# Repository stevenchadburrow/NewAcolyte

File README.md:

# NewAcolyte

This is the New Acolyte microcomputer.  

It runs a W65C02 microprocessor at 6.29 MHz, and has 64 KB of RAM and 32 KB of ROM available.  It can output 16-colors at a 256x240 resolution, or 4-colors at 512x240 resolution.  It supports PS/2 Keyboard and Mouse, Genesis Gamepad, square wave audio output, and SD Card through SPI adapter.  This New Acolyte uses the Xilinx XC9572XL CLPD, programmed using Xilinx ISE and 'xc3sprog'.  

Currently it's software includes the Scratchpad, Monitor, BASIC, and games including Tetra, Intruders, Missile, Galian, and Knave.

(Bodge wire connects V-SYNC to /NMI. Additional pull-up resistors on JOY-UP, JOY-DOWN, JOY-BUTTON1, and JOY-BUTTON2. Additional pull-down resistor on ROM-BANK.)

<br>
<br>
<br>
<br>
<br>

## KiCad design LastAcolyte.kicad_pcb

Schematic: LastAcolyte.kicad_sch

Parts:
C1: C_Polarized_US; CP_Elec_6.3x5.4
C2, C16: C-Polarized-US; CP_Elec_4x5.4
C3, C4, C5, C6, C7, C8, C9, C10, C11, C12, C13, C14, C17, C18: C; C_1206_3216Metric_Pad1.33x1.80mm_HandSolder
C15: C_Polarized_US; CP_Elec_4x5.4
D1: LED; LED_1206_3216Metric_Pad1.42x1.75mm_HandSolder
J1: USB_B; DualPowerSupply
J2: Mini-DIN-6; PS2_Din6
J3: AudioJack3; Jack_3.5mm_CUI_custom_SJ-3524-SMT_Horizontal
J4: DB15_Female_HighDensity; DSUB-15-HD_Female_Horizontal_P2.29x2.54mm_VGA
J5: Conn-01x06; SDcardPinSocket-Plus
J6, J7: Conn_02x10_Odd_Even; PinHeader_2x10_P2.54mm_Horizontal
J8: DB9_Male; DSUB-9-custom_Male_Horizontal_P2.77x2.84mm_EdgePinOffset7.7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
J9: Conn_02x05_Odd_Even; PinHeader_2x05_P2.54mm_Vertical
JP2: SolderJumper_2_Open; SolderJumper_Testing-2_P1.3mm_Open_Pad1.0x1.5mm
R1, R4, R5, R6, R7, R9, R10, R11, R12, R13, R14, R15, R16, R17, R18, R19, R20, R21, R22, R23, R24, R25, R26, R27: R_US; R_1206_3216Metric_Pad1.30x1.75mm_HandSolder
R2, R3, R8: R-US; R_1206_3216Metric_Pad1.30x1.75mm_HandSolder
SW1: SW_SPDT; SPDT-100SP1T2B4M6QE
SW2: SW_Push; SW_Tactile_SPST_Angled_PTS645Vx83-2LFS
TP1, TP2, TP3, TP4: TestPoint; ScrewHole-4-40
U1: W65C02SxPL; PLCC-44_THT-Socket
U2: IS62C1024AL-35; SSOP-32_11.305x20.495mm_P1.27mm
U3: SST39SF010-55; PLCC-32_THT-Socket
U4: LD1117S33; SOT-223-3_TabPin2
U5: XC9572XLVQ44; TQFP-44_10x10mm_P0.8mm
U6: 74HCT574; SOIC-20W_7.5x12.8mm_P1.27mm
U7: W65C22SxPL; PLCC-44_THT-Socket
U8: MCP130-xxxxSN; SOIC-8_3.9x4.9mm_P1.27mm
X1: CXO_DIP8; Oscillator_DIP-8-custom

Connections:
+3.3V: C10.1, C11.1, C12.1, C15.1, J9.4, R1.2, R9.1, R10.1, R11.1, R12.1, U4.2 (VO), U5.15 (VCC), U5.26 (VCCIO), U5.35 (VCC)
+5V: C1.1, C3.1, C4.1, C5.1, C6.1, C7.1, C8.1, C9.1, C13.1, C14.1, C17.1, C18.1, J2.4, J5.2, J6.1, J6.19, J7.2, J7.19, J8.5, JP2.2 (B), R4.1, R5.1, R6.1, R7.2, R18.1, R19.2, R20.2, R22.2, R23.1, R24.1, R25.2, R26.2, R27.2, SW1.2 (B), U1.9 (VDD), U1.37 (VDD), U2.1 (A18), U2.30 (A17), U2.32 (VCC), U3.31 (PGM), U3.32 (VCC), U4.3 (VI), U6.20 (VCC), U7.21 (VDD), U7.26 (CS1), U8.2 (VDD), X1.8 (Vcc)
/A0: U1.10 (A0), U2.12 (A0), U3.12 (A0), U6.12 (Q7), U7.42 (RS0)
/A1: U1.11 (A1), U2.11 (A1), U3.11 (A1), U6.13 (Q6), U7.41 (RS1)
/A2: U1.13 (A2), U2.10 (A2), U3.10 (A2), U6.14 (Q5), U7.40 (RS2)
/A3: U1.14 (A3), U2.9 (A3), U3.9 (A3), U6.15 (Q4), U7.39 (RS3)
/A4: U1.15 (A4), U2.8 (A4), U3.8 (A4), U6.16 (Q3)
/A5: U1.16 (A5), U2.7 (A5), U3.7 (A5), U6.17 (Q2)
/A6: U1.17 (A6), U2.6 (A6), U3.6 (A6), U6.18 (Q1)
/A7: U1.18 (A7), U2.5 (A7), U3.5 (A7), U6.19 (Q0)
/A8: U1.19 (A8), U2.27 (A8), U3.27 (A8), U5.14 (P20), U6.9 (D7)
/A9: U1.20 (A9), U2.26 (A9), U3.26 (A9), U5.16 (P22), U6.8 (D6)
/A10: U1.21 (A10), U2.23 (A10), U3.23 (A10), U5.18 (P24), U6.7 (D5)
/A11: U1.22 (A11), U2.25 (A11), U3.25 (A11), U5.19 (P25), U6.6 (D4)
/A12: U1.25 (A12), U2.4 (A12), U3.4 (A12), U5.20 (P26), U6.5 (D3)
/A13: U1.26 (A13), U2.28 (A13), U3.28 (A13), U5.21 (P27), U6.4 (D2)
/A14: U1.27 (A14), U2.3 (A14), U5.22 (P28), U6.3 (D1)
/A15: U1.28 (A15), U2.31 (A15), U5.23 (P29), U6.2 (D0)
A16: U2.2 (A16), U5.27 (P33)
AUDIO-CH-A: C2.1, U7.18 (PB7)
AUDIO-CH-B: C16.1, U7.19 (CB1)
AUDIO-NEG-A: C2.2, R2.2
AUDIO-NEG-B: C16.2, R8.2
AUDIO-OUT: J3.R, J3.T, R2.1, R3.1, R8.1
BE: U1.40 (BE), U1.43 (ϕ2O)
BLUE: J4.3, R15.2, R21.2
CB2: J7.17, U7.20 (CB2)
D0: J7.4, U1.36 (D0), U2.13 (DQ0), U3.13 (D0), U5.13 (P19), U7.36 (D0)
D1: J7.6, U1.35 (D1), U2.14 (DQ1), U3.14 (D1), U5.12 (P18), U7.35 (D1)
D2: J7.8, U1.34 (D2), U2.15 (DQ2), U3.15 (D2), U5.8 (P14), U7.34 (D2)
D3: J7.10, U1.33 (D3), U2.17 (DQ3), U3.17 (D3), U5.7 (P13), U7.32 (D3)
D4: J7.12, U1.32 (D4), U2.18 (DQ4), U3.18 (D4), U5.6 (P12), U7.31 (D4)
D5: J7.14, U1.31 (D5), U2.19 (DQ5), U3.19 (D5), U5.5 (P11), U7.30 (D5)
D6: J7.16, U1.30 (D6), U2.20 (DQ6), U3.20 (D6), U5.3 (P9), U7.29 (D6)
D7: J7.18, U1.29 (D7), U2.21 (DQ7), U3.21 (D7), U5.2 (P8), U7.28 (D7)
GND: C1.2, C3.2, C4.2, C5.2, C6.2, C7.2, C8.2, C9.2, C10.2, C11.2, C12.2, C13.2, C14.2, C15.2, C17.2, C18.2, D1.1 (K), J1.4 (GND), J1.5 (Shield), J1.7 (Barrel_GND), J2.3, J3.S, J4.5, J4.6, J4.7, J4.8, J4.10, J5.1, J6.3, J6.5, J6.7, J6.9, J6.11, J6.13, J6.15, J6.17, J7.1, J7.20, J8.8, J9.2, J9.10, R3.2, SW1.4 (Shield), SW2.2, TP1.1, TP2.1, TP3.1, TP4.1, U1.1 (VSS), U1.23 (VSS), U1.24 (VSS), U2.16 (VSS), U3.1 (A18), U3.2 (A16), U3.3 (A15), U3.16 (GND), U3.30 (A17), U4.1 (GND), U5.4 (GND), U5.17 (GND), U5.25 (GND), U6.10 (GND), U7.1 (VSS), U8.4 (VSS), X1.4 (GND)
GREEN: J4.2, R14.2, R17.2
H-SYNC: J4.13, U5.32 (P38)
JOY-BUTTON1: J6.10, J8.6, U7.6 (PA4)
JOY-BUTTON2: J6.12, J8.9, U7.7 (PA5)
JOY-DOWN: J6.4, J8.2, U7.3 (PA1)
JOY-LEFT: J6.6, J8.3, R27.1, U7.4 (PA2)
JOY-RIGHT: J6.8, J8.4, R26.1, U7.5 (PA3)
JOY-SELECT: J8.7, U7.14 (PB3)
JOY-UP: J6.2, J8.1, U7.2 (PA0)
JTAG-TCK: J9.1, R10.2, U5.11 (TCK)
JTAG-TDI: J9.9, R12.2, U5.9 (TDI)
JTAG-TDO: J9.3, R9.2, U5.24 (TDO)
JTAG-TMS: J9.5, R11.2, U5.10 (TMS)
KEY-CLOCK: J2.5, J6.18, R23.2, U7.44 (CA1)
KEY-DATA: J2.1, J6.16, R24.2, U7.9 (PA7)
LAST: J7.7, U5.1 (I/O/GCK3), U7.27 (ϕ2)
LATCH: U5.38 (P44), U6.11 (Cp)
LED: D1.2 (A), R1.1
MCLK: U5.43 (I/O/GCK1), X1.5 (OUT)
MOUSE-CLOCK: J2.6, J6.20, R20.1, U7.43 (CA2)
MOUSE-DATA: J2.2, J6.14, R19.1, U7.8 (PA6)
PHI2: U1.41 (ϕ0), U5.44 (I/O/GCK2), U6.1 (OE)
PIX-BLUE: R15.1, U5.41 (P3)
PIX-GREEN: R14.1, U5.40 (P2)
PIX-INT: R16.1, R17.1, R21.1, U5.42 (P4)
PIX-RED: R13.1, U5.39 (P1)
POWER-IN: J1.1 (VBUS), J1.6 (Barrel_VCC), JP2.1 (A), SW1.1 (A)
RAM-BANK: U5.37 (P43), U7.15 (PB4)
RDY: J7.13, R7.1, U1.3 (RDY)
RED: J4.1, R13.2, R16.2
ROM-BANK: U3.29 (A14), U7.16 (PB5)
SPI-CLK: J5.5, U7.10 (PB0)
SPI-MISO: J5.3, R25.1, U7.17 (PB6)
SPI-MOSI: J5.4, U7.12 (PB1)
SPI-SDCARD: J5.6, U7.13 (PB2)
SYNC: J7.15, U1.8 (SYNC)
V-SYNC: J4.14, U5.31 (P37)
~IRQ: R22.1, U1.5 (~IRQ), U7.23 (~IRQ)
~NMI: J7.9, R4.2, U1.7 (~NMI)
~OE: U2.24 (OE#), U3.24 (OE), U5.36 (I/O/GTS1)
~PHI2: J7.5, U1.4 (ϕ1)
~RAM: U2.22 (CE#), U5.28 (P34)
~RES: J7.3, R18.2, SW2.1, U1.44 (~RES), U7.37 (~RES), U8.1 (~RST)
~ROM: U3.22 (CE), U5.29 (P35)
~RW: R6.2, U1.38 (R/~W), U5.33 (I/O/GSR), U7.24 (R/~W)
~SO: J7.11, R5.2, U1.42 (~SO)
~VIA: U5.30 (P36), U7.25 (~CS2)
~WE: U2.29 (WE#), U5.34 (I/O/GTS2)

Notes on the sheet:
0.1uF Bypass Capacitors near VCC of each IC
Acolyte Computer Steven Chad Burrow 2023, Public Domain
Can also use AS6C1008, (and the 62256)
Optional Resistor
Can also use SST39SF010, (and the 27C512)
Micro SD Card Adapter
Sega Genesis Controller
EXPANSION
http://falstad.com/circuit/circuitjs.html?ctz=CQAgjCAMB0l3BWcMBMcUHYMGZIA4UA2ATmIxAUgpABZsKBTAWjDACgAlcFPcQqsDxDFCUMTSpIq06AjYBlcMRTgMowbzBqxEAGYBDADYBnBmJQKlK7NnVCbogSAMmzVC1w0hsabrxQIjuKSYjJyAOZ+3ggqXth4NKFskV5gylEoKInSbADuVqqiPJra7ABOIMWF3rbVVIRobBVVaLwOlfhiGJRNlXj+EjVFgwKUcHl9JUX9HbyQEy2dLSMTad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
Check all of these values with 3.3V
VGA Output
Pull-up resistors
BYPASS
ROM program code should be duplicated in both/all high banks
PS/2 Keyboard (and Mouse)
VGA graphics resolutions: 256x240 at 16-colors 512x240 at 4-colors PS/2 Keyboard and Mouse Genesis Controller SPI SD Card Square Wave Audio W65C02 running at 6.29 MHz 2KB System RAM 30KB Video RAM 32KB General RAM (2 banks of 16KB) 32KB Program ROM (2 banks of 16KB) Memory Map: $0000-$07FF = System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
Acolyte Computer Professor Steven Chad Burrow stevenchadburrow@gmail.com
Mounting Holes
JTAG connector

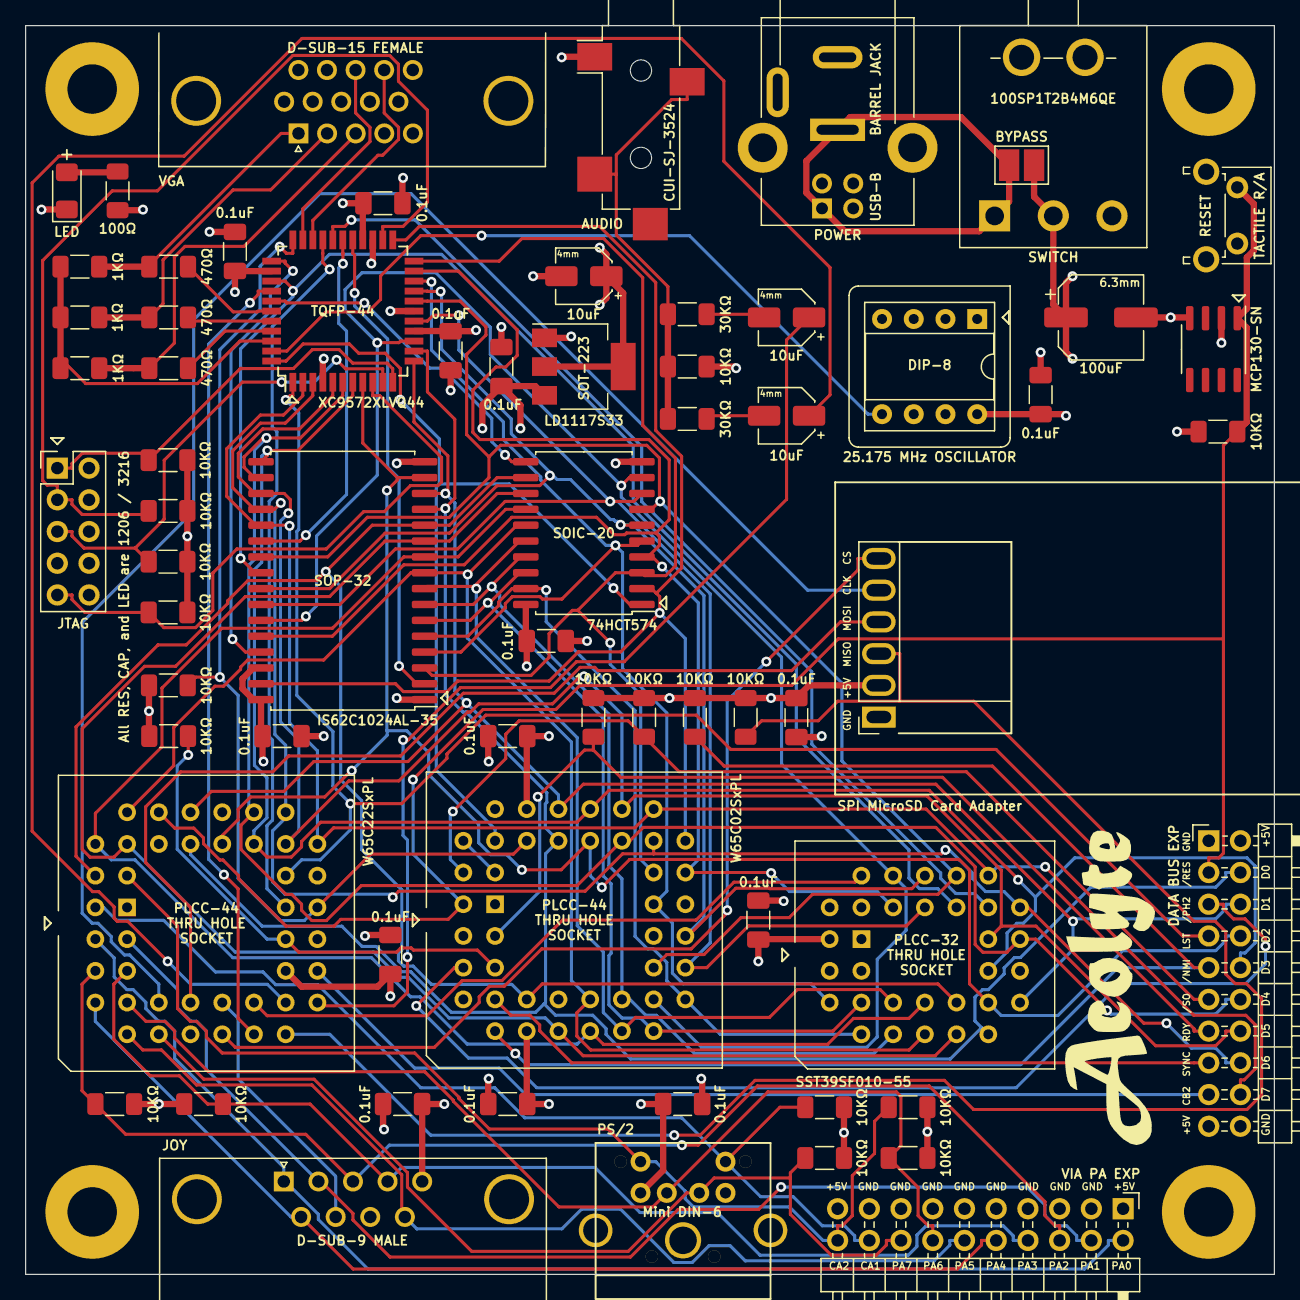
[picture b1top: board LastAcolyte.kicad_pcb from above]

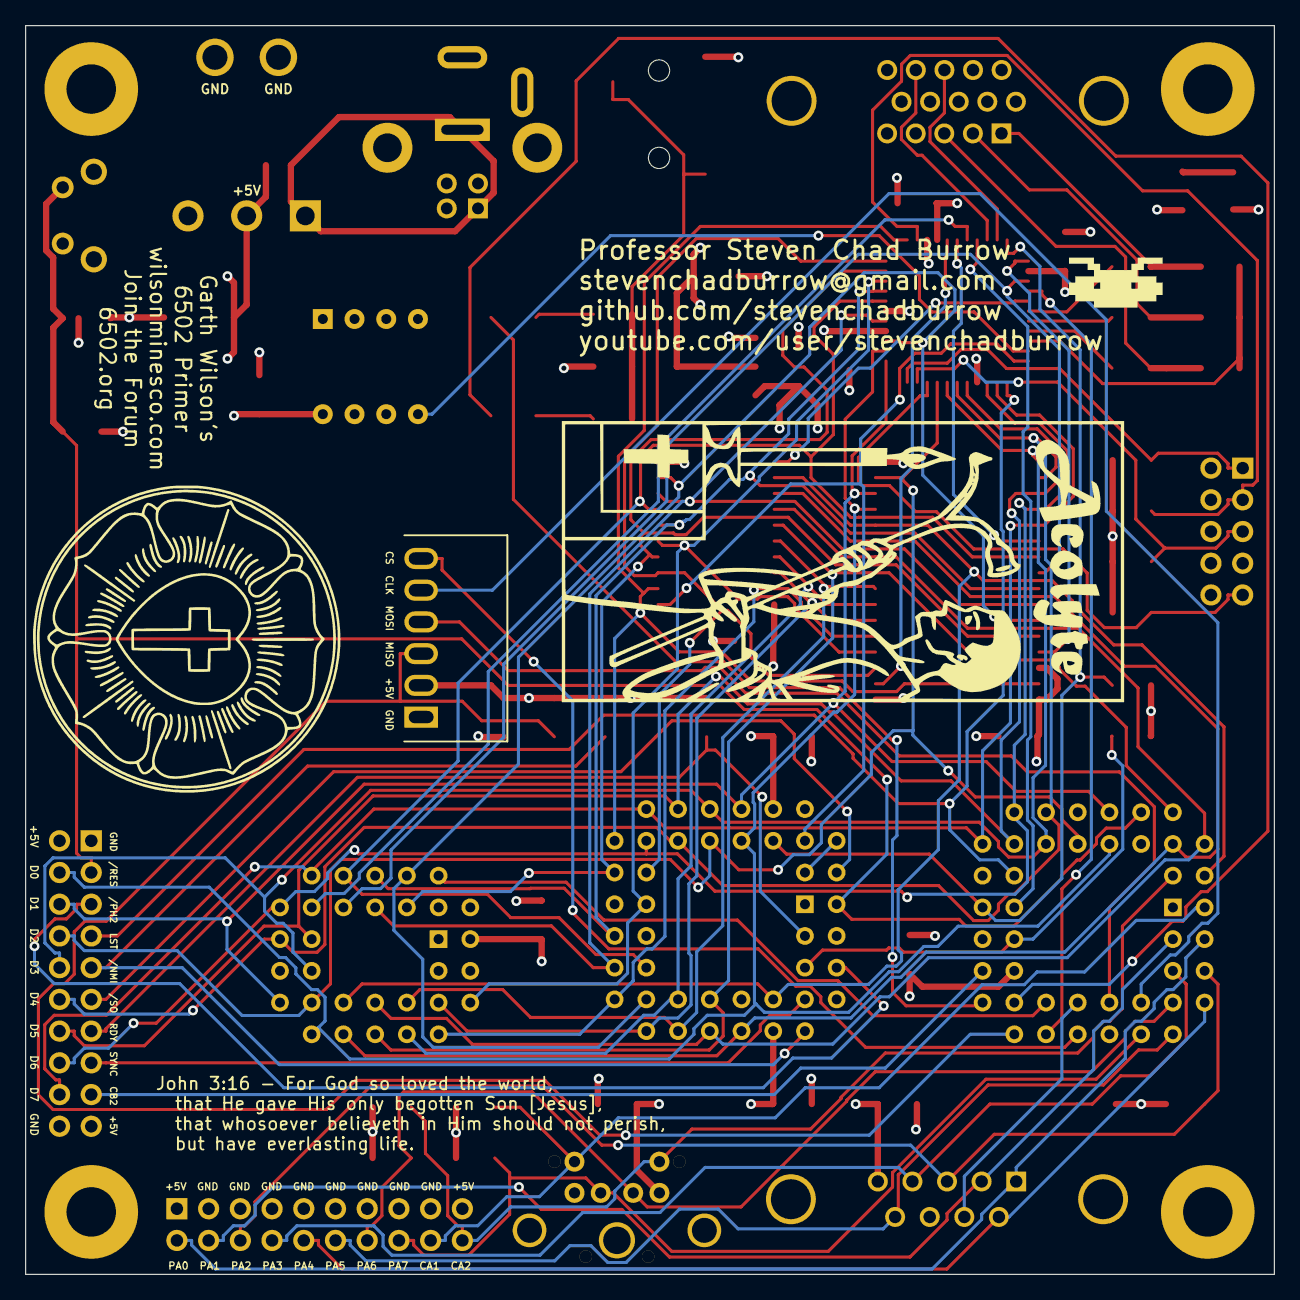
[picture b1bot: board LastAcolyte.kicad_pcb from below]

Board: 4 copper layers, 100.0 x 100.0 mm, 75 parts (3 on the bottom side), 84 nets.

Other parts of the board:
G101: LOGO; AcolyteLogoSmall
G102: LOGO; Mystery
G103: LOGO; LutheranRosePD
G104: LOGO; AcolyteName

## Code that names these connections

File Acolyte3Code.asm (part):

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; Black and White are always available, but other two
; colors are defined when entering that mode.

; VIA pins
; PA0 = JOY-UP
; PA1 = JOY-DOWN
; PA2 = JOY-LEFT (with 10K pull-up)
; PA3 = JOY-RIGHT (with 10K pull-up)
; PA4 = JOY-BUTTON1
; PA5 = JOY-BUTTON2
; PA6 = MOUSE-DATA
; PA7 = KEY-DATA
; CA1 = KEY-CLOCK
; CA2 = MOUSE-CLOCK
; PB0 = SPI-CLOCK
; PB1 = SPI-MOSI
; PB2 = SPI-CS (for SDCARD)
; PB3 = JOY-SELECT
; PB4 = RAM-BANK
; PB5 = ROM-BANK
; PB6 = SPI-MISO
; PB7 = AUDIO-CH-A
; CB1 = AUDIO-CH-B
; CB2 = Unused

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	JSR longdelay ; 100ms minimum delay
	JSR longdelay
	JSR longdelay
	LDA #%01000000 ; PA6 is output now
	STA via_da
	LDA #%00000000
	STA via_pah
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	JMP mouse_isr_normal
mouse_isr_normal
	LDA via_pah
	AND #%01000000				; read PA6 (without handshake)
	CLC	
	ROL A
	CLC
	ROR mouse_data				; shift mouse_code
	CLC
	ADC mouse_data				; add the PA6 bit into mouse_code
	STA mouse_data
	INC mouse_counter			; increment mouse_counter
	LDA mouse_counter
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	JMP mouse_isr				; if not, it's the mouse
key_isr_start	
	LDA via_pa
	AND #%10000000				; read PA7
	CLC	
	ROR key_data				; shift key_code
	CLC
	ADC key_data				; add the PA7 bit into key_code
	STA key_data
	INC key_counter				; increment key_counter
	LDA key_counter
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
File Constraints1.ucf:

NET address[0] LOC = P14;
NET address[1] LOC = P16;
NET address[2] LOC = P18;
NET address[3] LOC = P19;

NET address[4] LOC = P20;
NET address[5] LOC = P21;
NET address[6] LOC = P22;
NET address[7] LOC = P23;

NET addr16 LOC = P27;

NET ram LOC = P28;
NET rom LOC = P29;
NET via LOC = P30;

NET vsync LOC = P31;
NET hsync LOC = P32;

NET bank LOC = P37;
NET latch LOC = P38;

NET red LOC = P39;
NET green LOC = P40;
NET blue LOC = P41;
NET intensity LOC = P42;

NET data[7] LOC = P2;
NET data[6] LOC = P3;
NET data[5] LOC = P5;
NET data[4] LOC = P6;

NET data[3] LOC = P7;
NET data[2] LOC = P8;
NET data[1] LOC = P12;
NET data[0] LOC = P13;

NET master_clock LOC = P43;
NET phi2 LOC = P44;
NET last LOC = P1;

NET oe LOC = P36;
NET we LOC = P34;
NET rw LOC = P33;
